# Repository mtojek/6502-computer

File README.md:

# 6502-computer
Build a 6502 computer

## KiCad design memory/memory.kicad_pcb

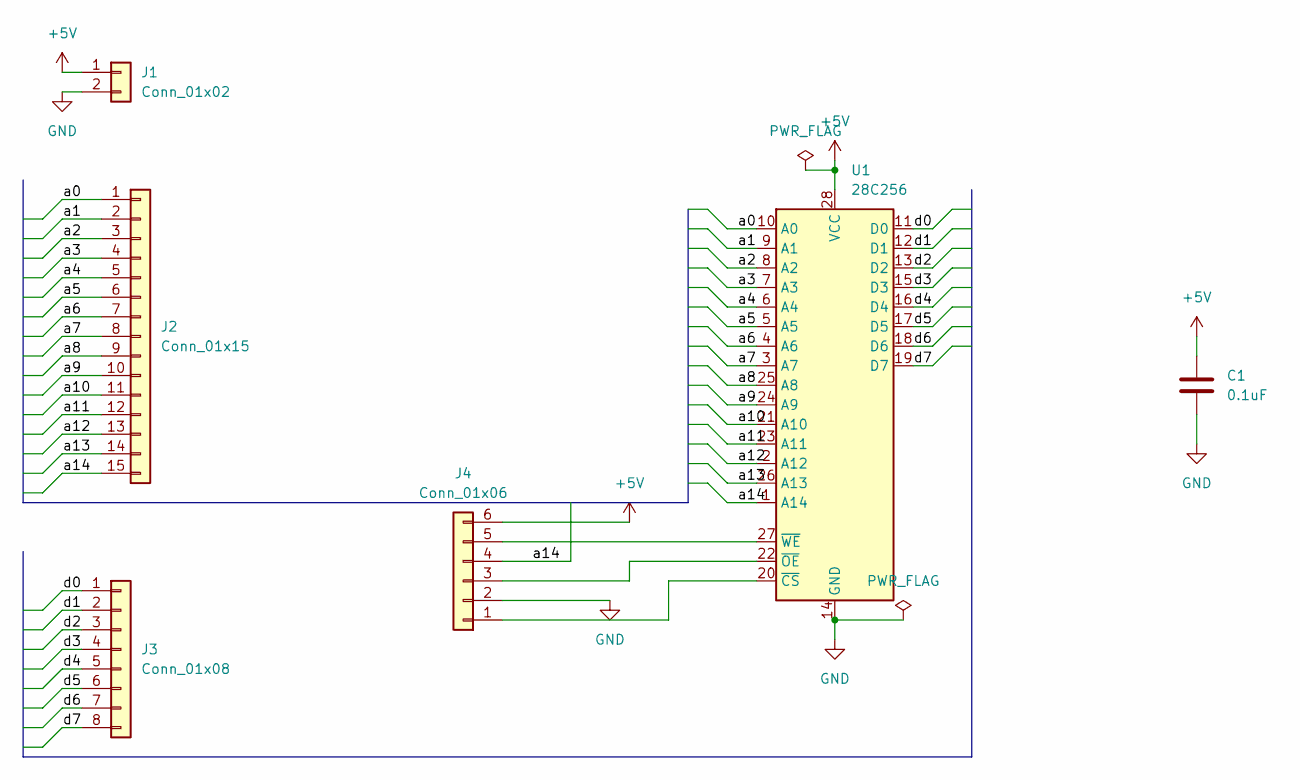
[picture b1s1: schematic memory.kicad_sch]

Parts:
C1: 0.1uF; C_Disc_D6.0mm_W2.5mm_P5.00mm
J1: Conn_01x02; PinHeader_1x02_P2.54mm_Horizontal
J2: Conn_01x15; PinHeader_1x15_P2.54mm_Horizontal
J3: Conn_01x08; PinHeader_1x08_P2.54mm_Horizontal
J4: Conn_01x06; PinHeader_1x06_P2.54mm_Vertical
U1: 28C256; DIP_Socket-28_W11.9_W12.7_W15.24_W17.78_W18.5_3M_228-1277-0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

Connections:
+5V: C1.2, J1.1, J4.6, U1.28 (VCC)
/a0: J2.1, U1.10 (A0)
/a1: J2.2, U1.9 (A1)
/a2: J2.3, U1.8 (A2)
/a3: J2.4, U1.7 (A3)
/a4: J2.5, U1.6 (A4)
/a5: J2.6, U1.5 (A5)
/a6: J2.7, U1.4 (A6)
/a7: J2.8, U1.3 (A7)
/a8: J2.9, U1.25 (A8)
/a9: J2.10, U1.24 (A9)
/a10: J2.11, U1.21 (A10)
/a11: J2.12, U1.23 (A11)
/a12: J2.13, U1.2 (A12)
/a13: J2.14, U1.26 (A13)
/a14: J2.15, J4.4, U1.1 (A14)
/d0: J3.1, U1.11 (D0)
/d1: J3.2, U1.12 (D1)
/d2: J3.3, U1.13 (D2)
/d3: J3.4, U1.15 (D3)
/d4: J3.5, U1.16 (D4)
/d5: J3.6, U1.17 (D5)
/d6: J3.7, U1.18 (D6)
/d7: J3.8, U1.19 (D7)
GND: C1.1, J1.2, J4.2, U1.14 (GND)
unnamed: J4.1, U1.20 (~CS)
unnamed: J4.3, U1.22 (~OE)
unnamed: J4.5, U1.27 (~WE)

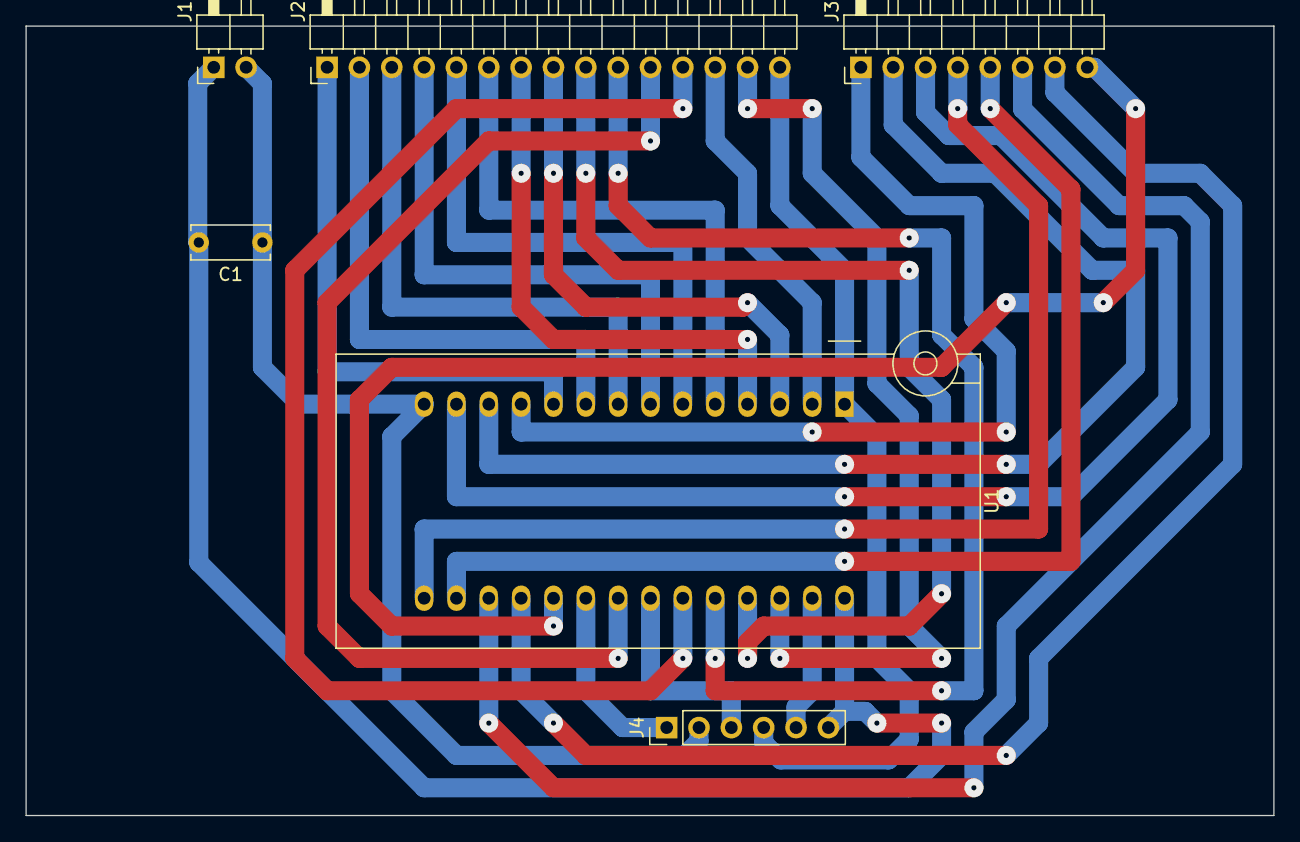
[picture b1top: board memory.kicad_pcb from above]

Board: 2 copper layers, 98.0 x 62.0 mm, 6 parts (0 on the bottom side), 28 nets.

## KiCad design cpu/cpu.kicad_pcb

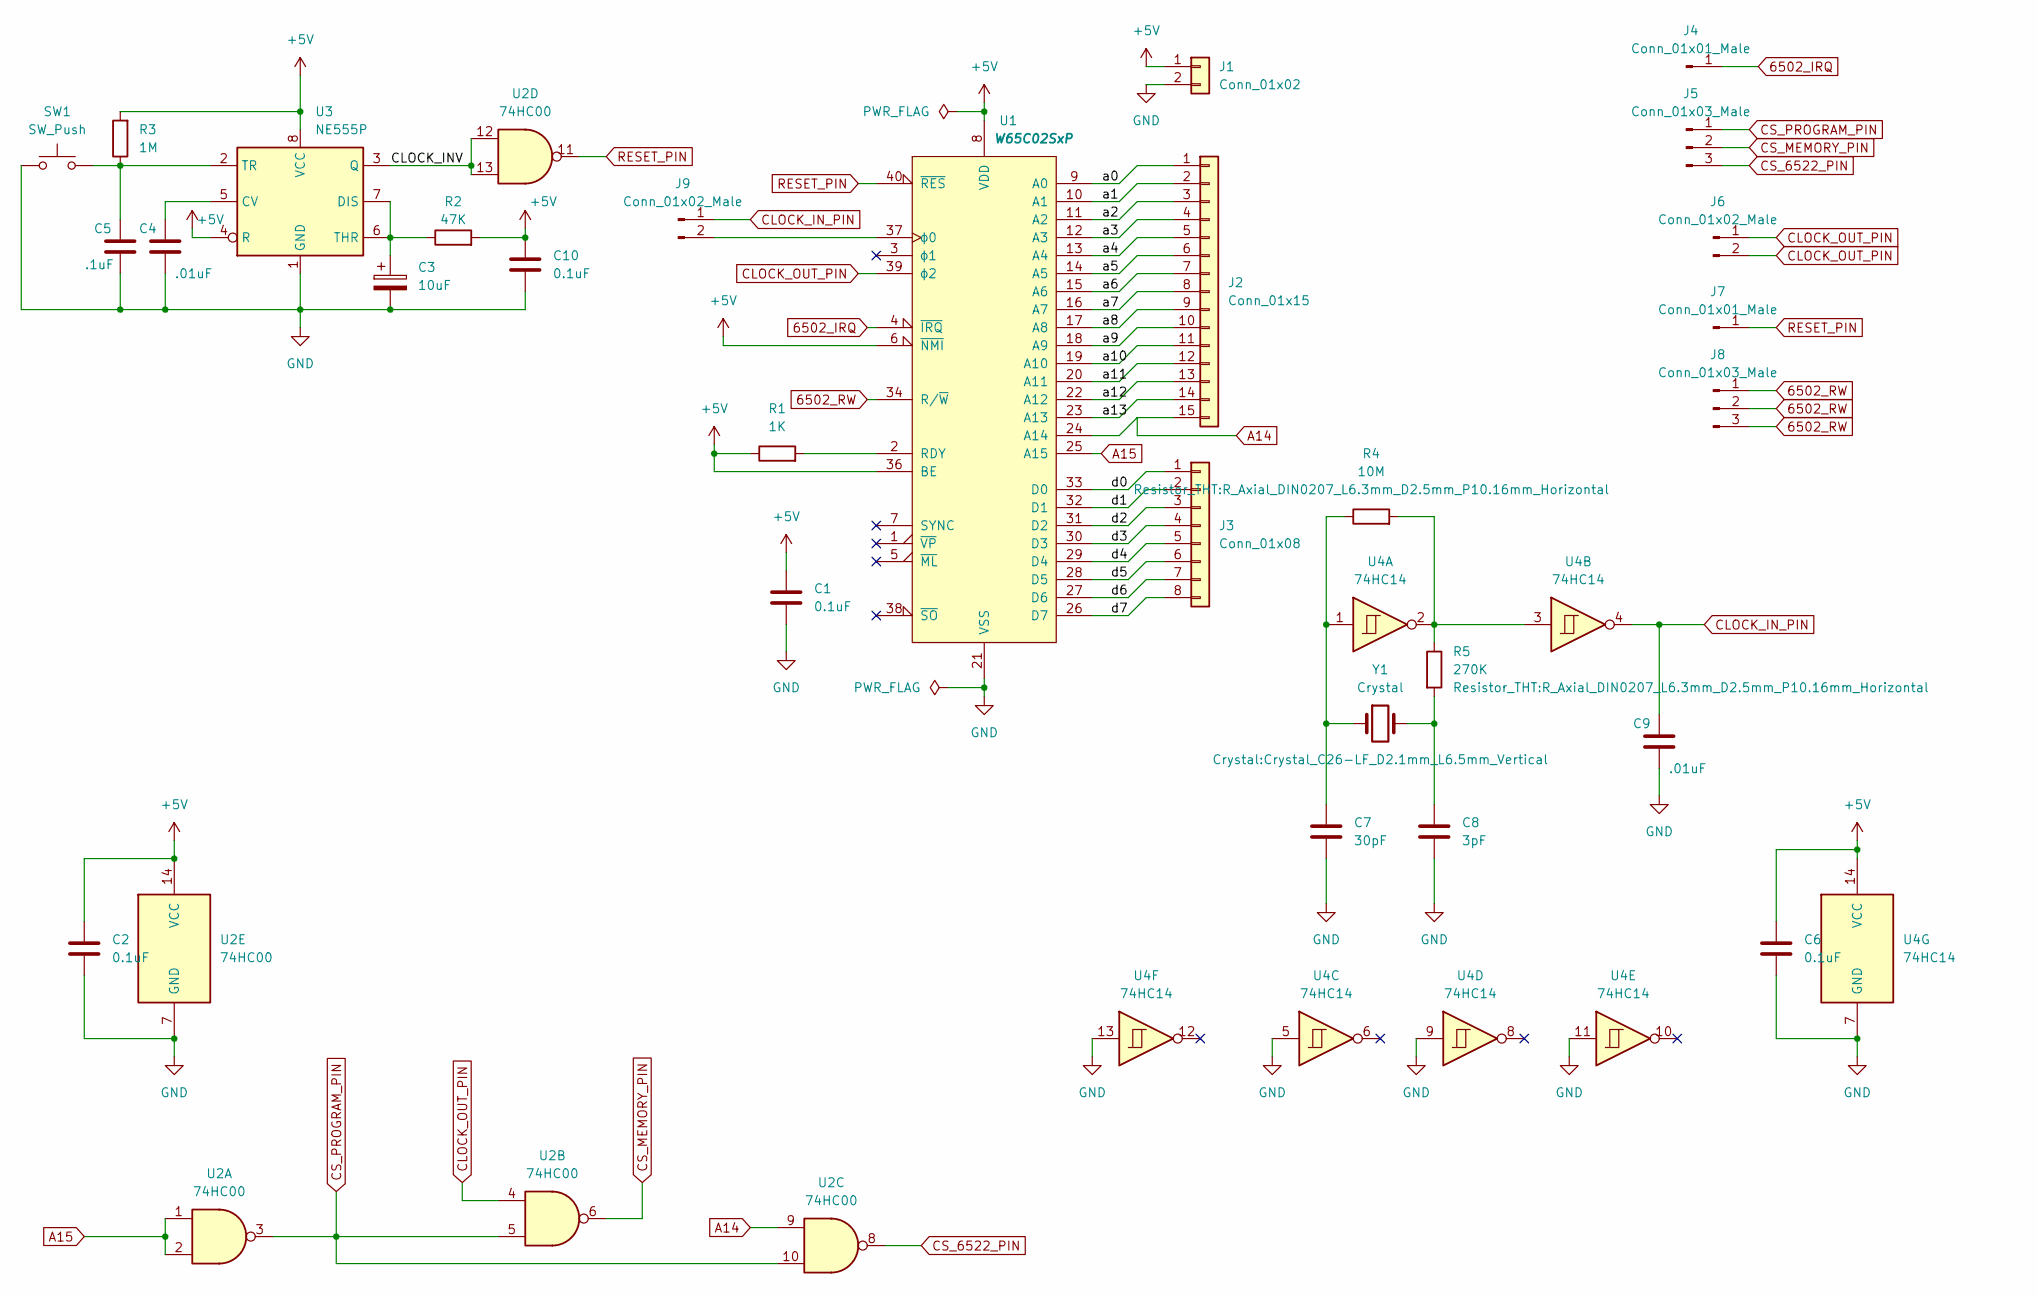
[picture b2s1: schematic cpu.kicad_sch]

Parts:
C1, C2, C6, C10: 0.1uF; C_Disc_D6.0mm_W2.5mm_P5.00mm
C3: 10uF; CP_Radial_D5.0mm_P2.50mm
C4, C9: .01uF; C_Rect_L7.0mm_W2.5mm_P5.00mm
C5: .1uF; C_Rect_L7.0mm_W2.5mm_P5.00mm
C7: 30pF; C_Disc_D3.0mm_W1.6mm_P2.50mm
C8: 3pF; C_Disc_D3.0mm_W1.6mm_P2.50mm
J1: Conn_01x02; PinHeader_1x02_P2.54mm_Horizontal
J2: Conn_01x15; PinHeader_1x15_P2.54mm_Horizontal
J3: Conn_01x08; PinHeader_1x08_P2.54mm_Horizontal
J4, J7: Conn_01x01_Male; PinHeader_1x01_P2.54mm_Vertical
J5, J8: Conn_01x03_Male; PinHeader_1x03_P2.54mm_Vertical
J6, J9: Conn_01x02_Male; PinHeader_1x02_P2.54mm_Vertical
R1: 1K; R_Axial_DIN0411_L9.9mm_D3.6mm_P12.70mm_Horizontal
R2: 47K; R_Axial_DIN0411_L9.9mm_D3.6mm_P12.70mm_Horizontal
R3: 1M; R_Axial_DIN0411_L9.9mm_D3.6mm_P12.70mm_Horizontal
R4: 10M; R_Axial_DIN0207_L6.3mm_D2.5mm_P10.16mm_Horizontal
R5: 270K; R_Axial_DIN0207_L6.3mm_D2.5mm_P10.16mm_Horizontal
SW1: SW_Push; SW_PUSH_6mm
U1: W65C02SxP; DIP-40_W15.24mm_Socket_LongPads
U2: 74HC00; DIP-14_W7.62mm_Socket_LongPads
U3: NE555P; DIP-8_W7.62mm
U4: 74HC14; DIP-14_W7.62mm_Socket_LongPads
Y1: Crystal; Crystal_C26-LF_D2.1mm_L6.5mm_Vertical

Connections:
6502_IRQ: J4.1, U1.4 (~IRQ)
6502_RW: J8.1, J8.2, J8.3, U1.34 (R/~W)
+5V: C1.2, C2.2, C6.2, C10.2, J1.1, R1.1, R2.2, R3.2, U1.6 (~NMI), U1.8 (VDD), U1.36 (BE), U2.14 (VCC), U3.4 (R), U3.8 (VCC), U4.14 (VCC)
/CLOCK_INV: U2.12, U2.13, U3.3 (Q)
/a0: J2.1, U1.9 (A0)
/a1: J2.2, U1.10 (A1)
/a2: J2.3, U1.11 (A2)
/a3: J2.4, U1.12 (A3)
/a4: J2.5, U1.13 (A4)
/a5: J2.6, U1.14 (A5)
/a6: J2.7, U1.15 (A6)
/a7: J2.8, U1.16 (A7)
/a8: J2.9, U1.17 (A8)
/a9: J2.10, U1.18 (A9)
/a10: J2.11, U1.19 (A10)
/a11: J2.12, U1.20 (A11)
/a12: J2.13, U1.22 (A12)
/a13: J2.14, U1.23 (A13)
/d0: J3.1, U1.33 (D0)
/d1: J3.2, U1.32 (D1)
/d2: J3.3, U1.31 (D2)
/d3: J3.4, U1.30 (D3)
/d4: J3.5, U1.29 (D4)
/d5: J3.6, U1.28 (D5)
/d6: J3.7, U1.27 (D6)
/d7: J3.8, U1.26 (D7)
A14: J2.15, U1.24 (A14), U2.9
A15: U1.25 (A15), U2.1, U2.2
CLOCK_IN_PIN: C9.1, J9.1, U4.4
CLOCK_OUT_PIN: J6.1, J6.2, U1.39 (ϕ2), U2.4
CS_6522_PIN: J5.3, U2.8
CS_MEMORY_PIN: J5.2, U2.6
CS_PROGRAM_PIN: J5.1, U2.3, U2.5, U2.10
GND: C1.1, C2.1, C3.2, C4.2, C5.2, C6.1, C7.1, C8.1, C9.2, C10.1, J1.2, SW1.1, U1.21 (VSS), U2.7 (GND), U3.1 (GND), U4.5, U4.7 (GND), U4.9, U4.11, U4.13
unnamed: C3.1, R2.1, U3.6 (THR), U3.7 (DIS)
unnamed: C4.1, U3.5 (CV)
unnamed: C5.1, R3.1, SW1.2, U3.2 (TR)
unnamed: C7.2, R4.1, U4.1, Y1.1
unnamed: C8.2, R5.2, Y1.2
unnamed: R1.2, U1.2 (RDY)
unnamed: R4.2, R5.1, U4.2, U4.3
unnamed: J9.2, U1.37 (ϕ0)
RESET_PIN: J7.1, U1.40 (~RES), U2.11

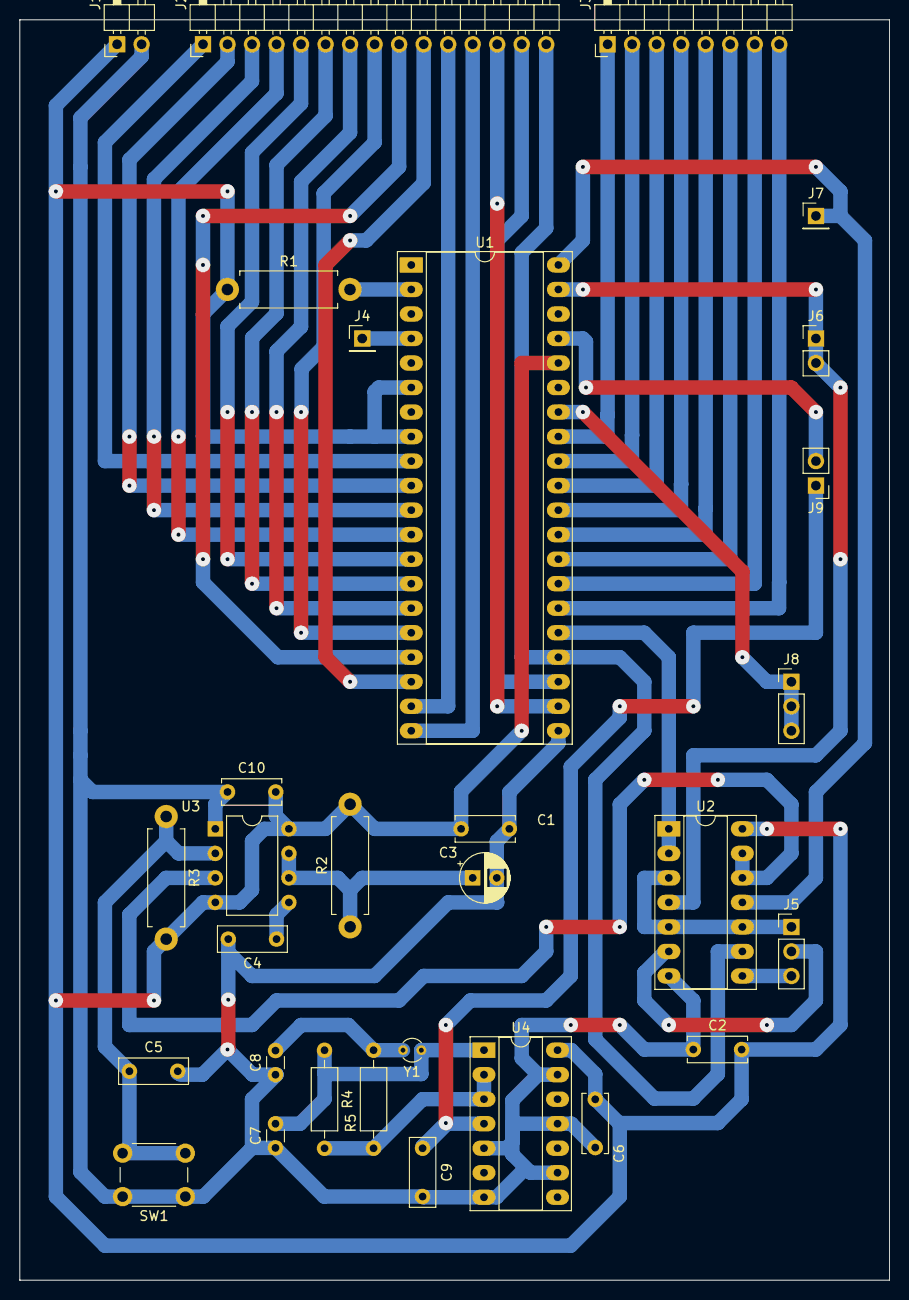
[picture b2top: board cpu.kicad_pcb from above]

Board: 2 copper layers, 90.1 x 130.6 mm, 30 parts (0 on the bottom side), 43 nets.

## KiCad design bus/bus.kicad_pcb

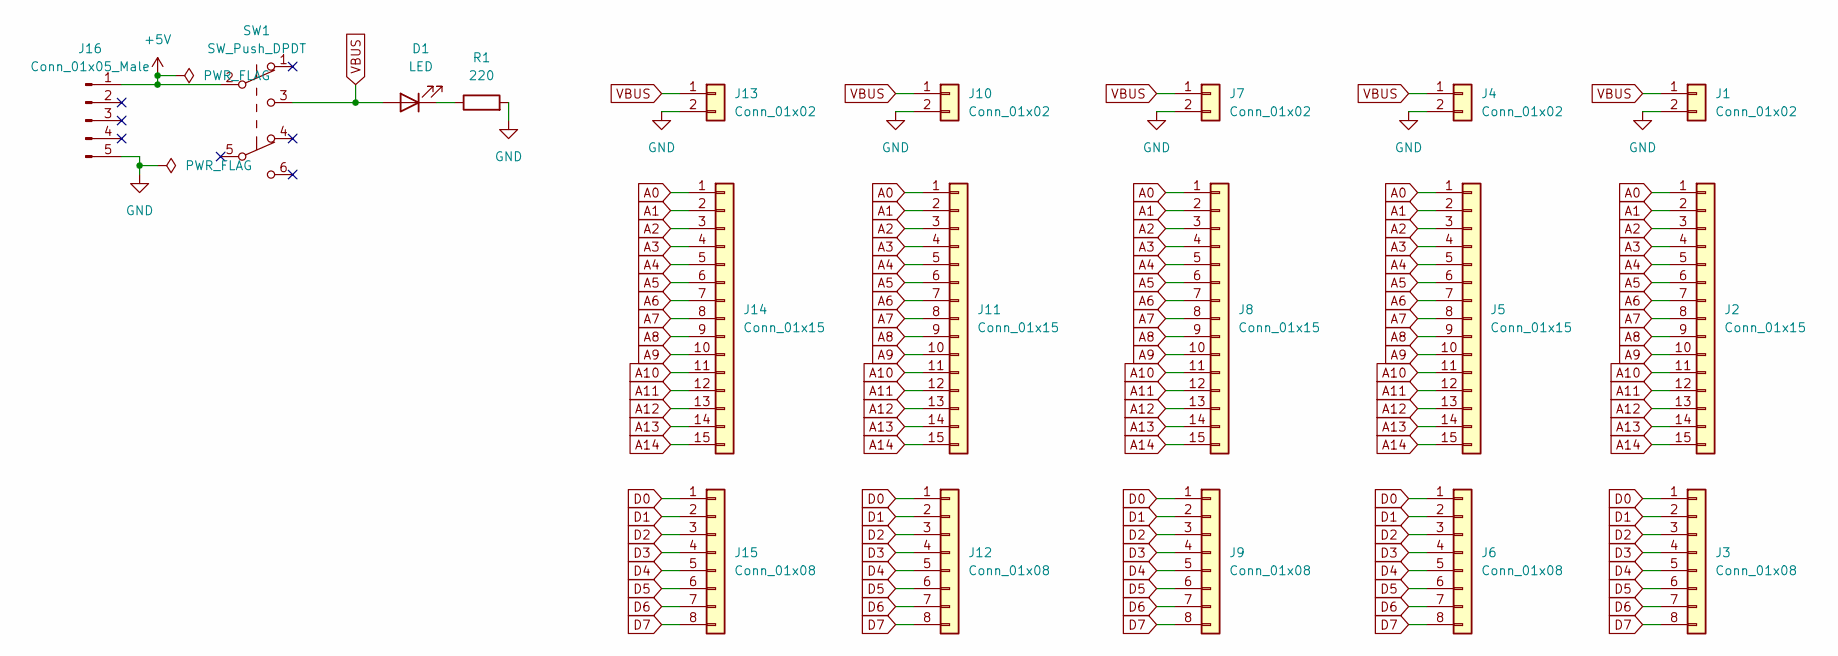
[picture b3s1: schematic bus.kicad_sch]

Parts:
D1: LED; LED_D5.0mm
J1, J4, J7, J10, J13: Conn_01x02; PinSocket_1x02_P2.54mm_Vertical
J2, J5, J8, J11, J14: Conn_01x15; PinSocket_1x15_P2.54mm_Vertical
J3, J6, J9, J12, J15: Conn_01x08; PinSocket_1x08_P2.54mm_Vertical
J16: Conn_01x05_Male; PinSocket_1x05_P2.54mm_Vertical
R1: 220; R_Axial_DIN0309_L9.0mm_D3.2mm_P12.70mm_Horizontal
SW1: SW_Push_DPDT; SW_E-Switch_EG1271_DPDT

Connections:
+5V: J16.1, SW1.2 (B)
A0: J2.1, J5.1, J8.1, J11.1, J14.1
A1: J2.2, J5.2, J8.2, J11.2, J14.2
A2: J2.3, J5.3, J8.3, J11.3, J14.3
A3: J2.4, J5.4, J8.4, J11.4, J14.4
A4: J2.5, J5.5, J8.5, J11.5, J14.5
A5: J2.6, J5.6, J8.6, J11.6, J14.6
A6: J2.7, J5.7, J8.7, J11.7, J14.7
A7: J2.8, J5.8, J8.8, J11.8, J14.8
A8: J2.9, J5.9, J8.9, J11.9, J14.9
A9: J2.10, J5.10, J8.10, J11.10, J14.10
A10: J2.11, J5.11, J8.11, J11.11, J14.11
A11: J2.12, J5.12, J8.12, J11.12, J14.12
A12: J2.13, J5.13, J8.13, J11.13, J14.13
A13: J2.14, J5.14, J8.14, J11.14, J14.14
A14: J2.15, J5.15, J8.15, J11.15, J14.15
D0: J3.1, J6.1, J9.1, J12.1, J15.1
D1: J3.2, J6.2, J9.2, J12.2, J15.2
D2: J3.3, J6.3, J9.3, J12.3, J15.3
D3: J3.4, J6.4, J9.4, J12.4, J15.4
D4: J3.5, J6.5, J9.5, J12.5, J15.5
D5: J3.6, J6.6, J9.6, J12.6, J15.6
D6: J3.7, J6.7, J9.7, J12.7, J15.7
D7: J3.8, J6.8, J9.8, J12.8, J15.8
GND: J1.2, J4.2, J7.2, J10.2, J13.2, J16.5, R1.2
unnamed: D1.1 (K), R1.1
VBUS: D1.2 (A), J1.1, J4.1, J7.1, J10.1, J13.1, SW1.3 (C)

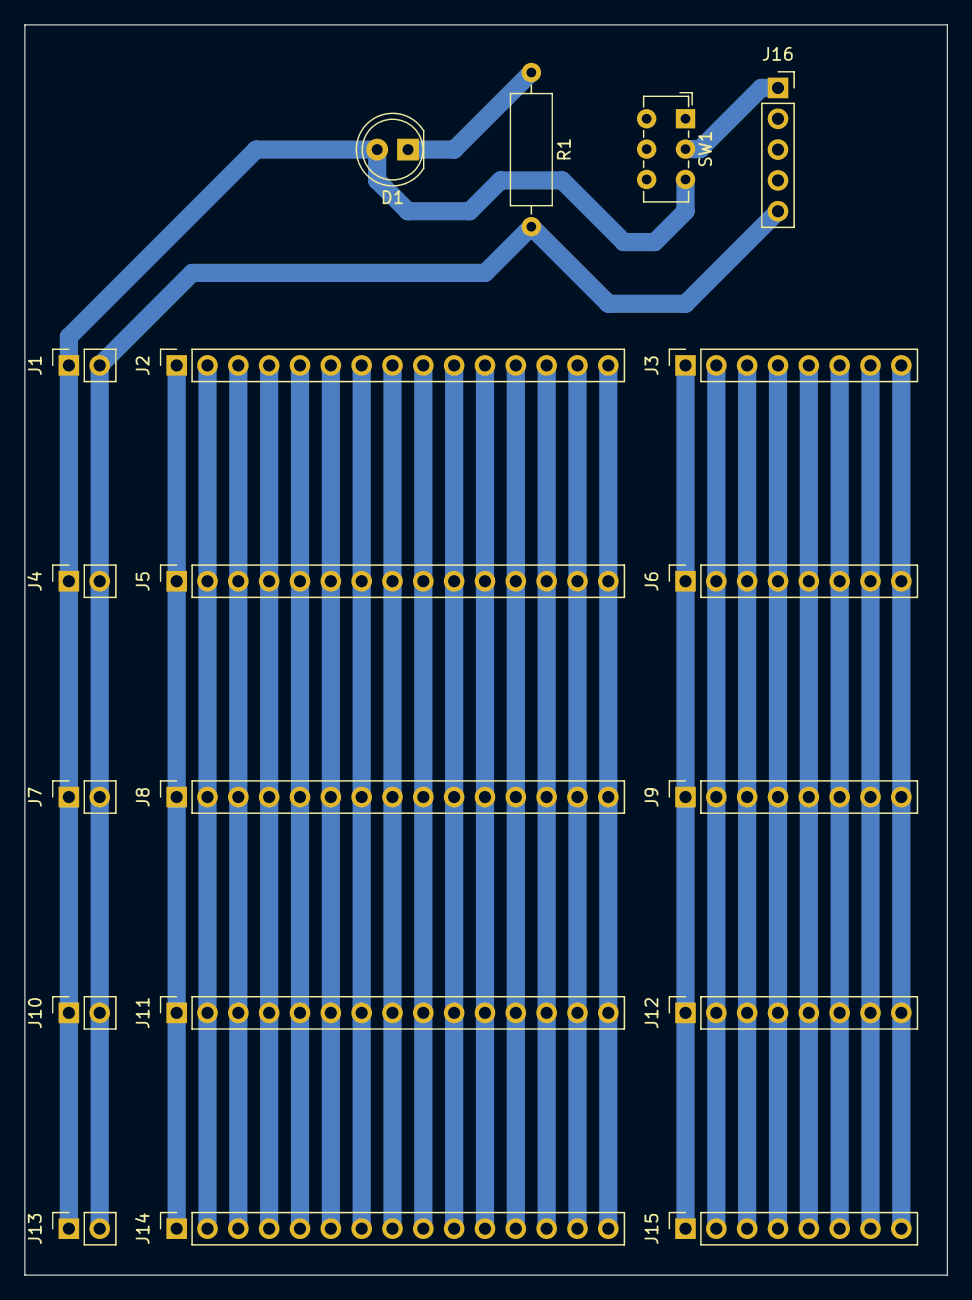
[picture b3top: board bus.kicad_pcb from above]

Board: 2 copper layers, 76.0 x 103.0 mm, 19 parts (0 on the bottom side), 27 nets.

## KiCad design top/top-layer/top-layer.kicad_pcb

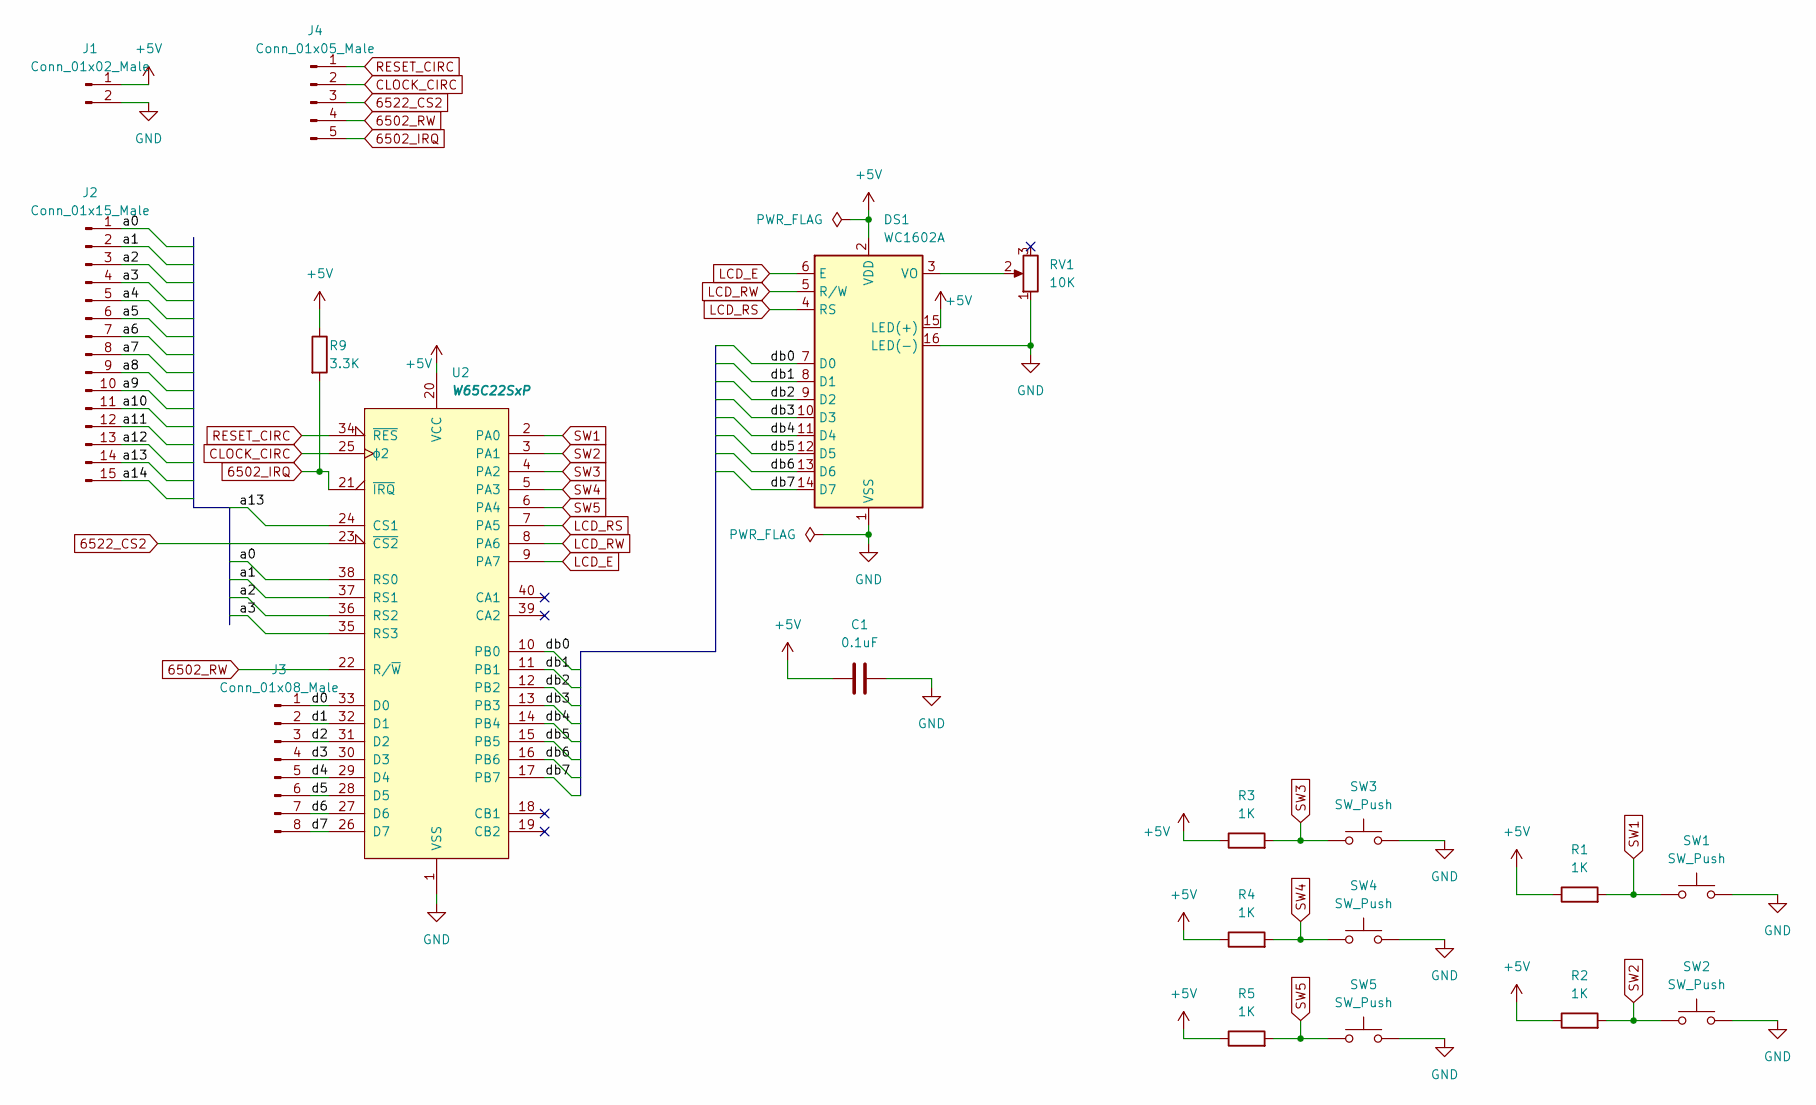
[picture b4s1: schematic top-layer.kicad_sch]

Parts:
C1: 0.1uF; C_Disc_D6.0mm_W2.5mm_P5.00mm
DS1: WC1602A
J1: Conn_01x02_Male; PinHeader_1x02_P2.54mm_Horizontal
J2: Conn_01x15_Male; PinHeader_1x15_P2.54mm_Horizontal
J3: Conn_01x08_Male; PinHeader_1x08_P2.54mm_Horizontal
J4: Conn_01x05_Male; PinHeader_1x05_P2.54mm_Vertical
R1, R2, R3, R4, R5: 1K; R_Axial_DIN0309_L9.0mm_D3.2mm_P12.70mm_Horizontal
R9: 3.3K; R_Axial_DIN0207_L6.3mm_D2.5mm_P10.16mm_Horizontal
RV1: 10K; Potentiometer_Piher_PT-6-V_Vertical
SW1, SW2, SW3, SW4, SW5: SW_Push; SW_PUSH_6mm_H4.3mm
U2: W65C22SxP; DIP-40_W15.24mm_Socket_LongPads

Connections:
6502_IRQ: J4.5, R9.2, U2.21 (~IRQ)
6502_RW: J4.4, U2.22 (R/~W)
6522_CS2: J4.3, U2.23 (~CS2)
+5V: C1.1, DS1.2 (VDD), DS1.15 (LED(+)), J1.1, R1.1, R2.1, R3.1, R4.1, R5.1, R9.1, U2.20 (VCC)
/a0: J2.1, U2.38 (RS0)
/a1: J2.2, U2.37 (RS1)
/a2: J2.3, U2.36 (RS2)
/a3: J2.4, U2.35 (RS3)
/a4: J2.5
/a5: J2.6
/a6: J2.7
/a7: J2.8
/a8: J2.9
/a9: J2.10
/a10: J2.11
/a11: J2.12
/a12: J2.13
/a13: J2.14, U2.24 (CS1)
/a14: J2.15
/d0: J3.1, U2.33 (D0)
/d1: J3.2, U2.32 (D1)
/d2: J3.3, U2.31 (D2)
/d3: J3.4, U2.30 (D3)
/d4: J3.5, U2.29 (D4)
/d5: J3.6, U2.28 (D5)
/d6: J3.7, U2.27 (D6)
/d7: J3.8, U2.26 (D7)
/db0: DS1.7 (D0), U2.10 (PB0)
/db1: DS1.8 (D1), U2.11 (PB1)
/db2: DS1.9 (D2), U2.12 (PB2)
/db3: DS1.10 (D3), U2.13 (PB3)
/db4: DS1.11 (D4), U2.14 (PB4)
/db5: DS1.12 (D5), U2.15 (PB5)
/db6: DS1.13 (D6), U2.16 (PB6)
/db7: DS1.14 (D7), U2.17 (PB7)
CLOCK_CIRC: J4.2, U2.25 (ϕ2)
GND: C1.2, DS1.1 (VSS), DS1.16 (LED(-)), J1.2, RV1.1, SW1.2, SW2.2, SW3.2, SW4.2, SW5.2, U2.1 (VSS)
LCD_E: DS1.6 (E), U2.9 (PA7)
LCD_RS: DS1.4 (RS), U2.7 (PA5)
LCD_RW: DS1.5 (R/W), U2.8 (PA6)
unnamed: DS1.3 (VO), RV1.2
RESET_CIRC: J4.1, U2.34 (~RES)
SW1: R1.2, SW1.1, U2.2 (PA0)
SW2: R2.2, SW2.1, U2.3 (PA1)
SW3: R3.2, SW3.1, U2.4 (PA2)
SW4: R4.2, SW4.1, U2.5 (PA3)

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
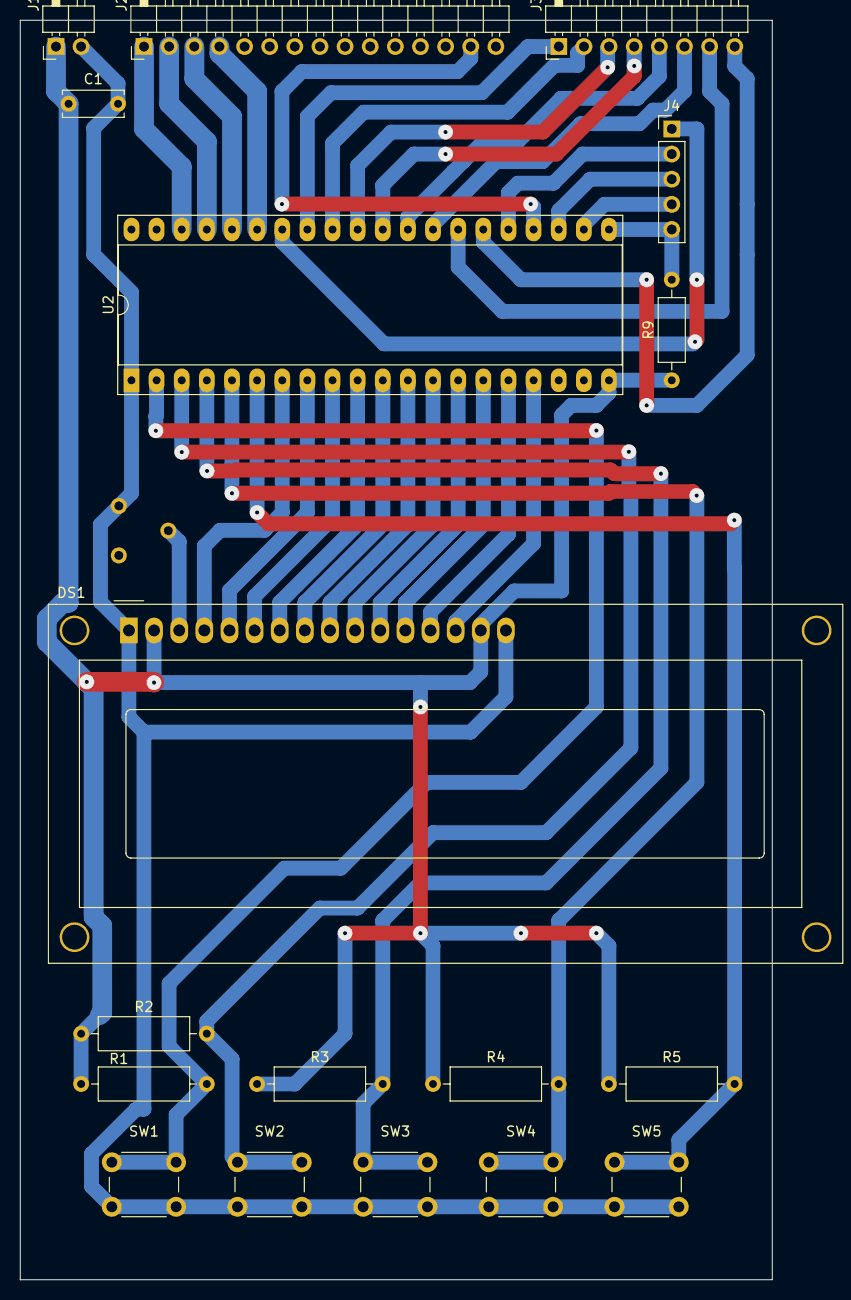
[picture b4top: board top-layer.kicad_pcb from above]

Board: 2 copper layers, 76.0 x 127.3 mm, 19 parts (1 on the bottom side), 37 nets.

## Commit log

2022-07-27 Top layer
2022-07-27 Move
2022-07-30 Empty project: memory
2022-07-31 WIP: memory
2022-08-01 Memory board
2022-08-01 WIP: cpu
2022-08-06 cpu: before routing
2022-08-07 CPU done
2022-08-07 Fix: memory
2022-08-07 Fix: top layer
2022-08-07 Done
2022-08-08 Fix: cpu
2022-08-08 Fix: bus layout
2022-09-26 Fit cpu
2022-10-13 Backup
